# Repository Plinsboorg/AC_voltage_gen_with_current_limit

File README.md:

# ac_current_generator

[schematic in PDF format](ac_current_generator.pdf)

## Video with the circuit description

https://youtu.be/Bf4n697qHjU

## Description
This particular circuit gives the MCU an abilty to generate AC current with required amplitude using only the DAC and 2 general purpose opamps.

## Usage
Insparation is that you can copy the repo and get a reusable circuit block. 

## Support
Please, contact me if you need any help <br>
Telegramm: https://t.me/Plinsboorg <br>
Email: dennis.yaskevich@proton.me <br>
I do commercial electronics design and consulting. <br>
I can also help you for free if you're doing an open hardware project.<br>

## Roadmap
I'll continue adding intresting analog circuits as separate repos

## Contributing
Please, submit your fixes if you see any mistakes or possible improvments.

## Authors and acknowledgment
This circuit is inspired by Flexi-TEER project
https://github.com/mdanderson03/Flexi-TEER

## License
[Attribution 4.0 International (CC BY 4.0)](https://creativecommons.org/licenses/by/4.0/)

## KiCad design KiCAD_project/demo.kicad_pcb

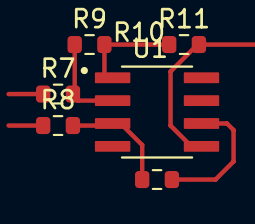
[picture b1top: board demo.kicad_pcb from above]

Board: 2 copper layers, 6 parts (0 on the bottom side), 5 nets.

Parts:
R7, R8: 20k; R_0603_1608Metric
R9, R10: 7.4k; R_0603_1608Metric
R11: 5k; R_0603_1608Metric
U1: AD8066ARZ-RL; SOIC127P599X175-8N

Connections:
LOAD_SYM: R11.2, U1.5 (+)
unnamed: R7.2, R9.1, U1.2 (-)
unnamed: R8.2, R10.1, U1.3 (+)
unnamed: R10.2, U1.6 (-), U1.7
unnamed: R9.2, R11.1, U1.1

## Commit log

2022-09-27 Project exported
2022-09-27 files rearranged
2022-09-27 relative path to library added
2022-09-27 extra files deleted
